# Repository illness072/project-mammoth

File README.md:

# Project 🦣

This keyboard was developed as a successor to the elephant42 and was originally planned to be released as mammoth42. However, during the development process, custom keyboards by other authors, Mammoth75 and Mammoth20, were released, and it seemed somewhat awkward to re-release the keyboard under the same name.
However, we could not give up our desire to use 🦣 as a companion to 🐘, so we decided to give it this name, taking care not to infringe on their names as much as possible.

# Still WIP, or Forever WIP?

This project is still in its infancy and is only about 20% of the way to the final product I have in mind. There are still a lot of unresolved bugs and issues, but even at this point, I think the keyboard is fun enough to use. Let's enjoy "being unfinished" together.

## Rough Milestones

1. [x] Works as USB HID with Pro Micro or as BLE HID with ISP1807micro and CR2032 battery.
1. [x] Operation as a left and right independent BLE device. The board might be modified to use Seeed XIAO BLE and the batteries might be modified to use NiMH rechargeable batteries.
1. [ ] Support for 34mm trackball.
1. (Still a secret.)

    :

## To be confirmed before manufacturing

The design currently uses two MCP23017-E/SS. These I/O expanders have long since been depleted from the market due to the recent semiconductor shortage and are currently priced at two to three times the normal price. To protect your wallet, it would be wise to wait for the stock to come back.

# BOM

## Main Boards

|Ref|Qty|Value or Part|Description|
|--|--|--|--|
||42|1N4148W|Fast Switching Diode|
||42|CPG151101S11-16|Kailh Switch Socket|
|U1,U2|2|MCP23017-E/SS|16-Bit I/O Expander|
||2|BM05B-ACHSS-A-GAN-ETF(LF)(SN)|JST ACH Connector 5P|

## Palm-rest Boards

|Ref|Qty|Value or Part|Description|
|--|--|--|--|
||2|BH-411-4P24|AAA Battery Holder|
||2|BM05B-ACHSS-A-GAN-ETF(LF)(SN)|JST ACH Connector 5P|
||2|SS-12D00G3|Slide Switch|
||2|Seeed Studio XIAO nRF52840||
|L1|2|100μH|Inductor|
|R1,R2|4|4.6kΩ|Resistor|
|C1|2|47μF|Capacitor|
|C2|2|22μF|Capacitor|
|D1|2|1S4|Schotky barrier diode|
|HT7733A|2|HT7733A|PFM Step-up DC/DC Converter|
|TRRS|0|MJ-4PP-9|TRRS Jack (Optional:2)|

## Cables

|Qty|Value or Part|Description|
|--|--|--|
|4|ACHR-05V-A-S|JST ACH Connector Housing 5P|
|10|01SACHSACH-30L-150|JST ACH Connector Contact(SACH-003G-P0.2) Cable|

# Where's the firmware?

Not yet.

# License?

Beerware!!

Come drink beer in Tokyo with me!! 🍺🍺🍺

# Poor English?

Sorry, it's DeepL Translate.

# [PR] Sponsored by PCBWay

Project 🦣 is currently prototyping with support from PCBWay (https://www.pcbway.com/).
We found the silks to be more accurate and beautiful than those of various PCB makers in the same price range.

If you are in doubt about which PCB manufacturer to manufacture, PCBWay, with its experience in manufacturing 🦣, may be a good choice.

Thanks a lot PCBWay!

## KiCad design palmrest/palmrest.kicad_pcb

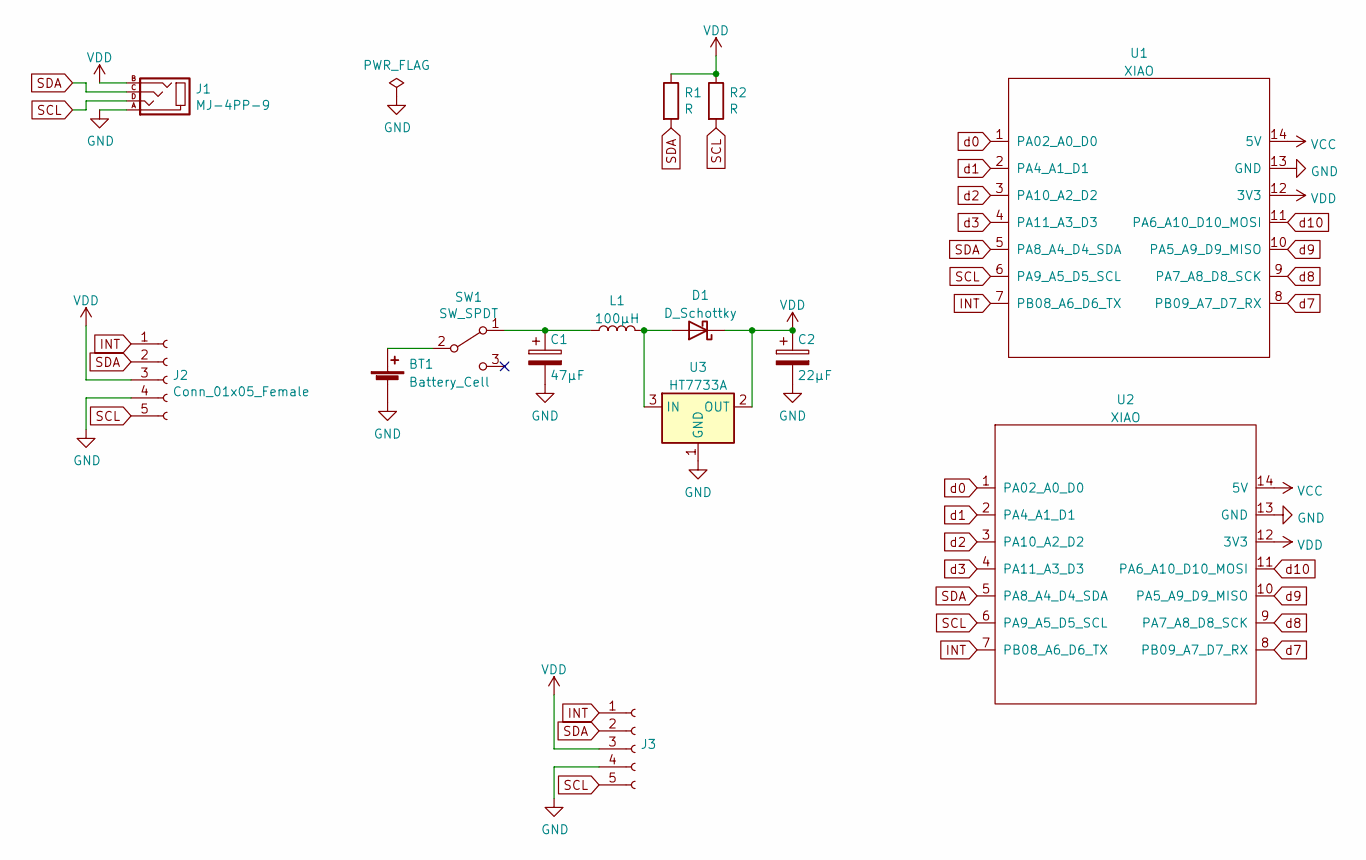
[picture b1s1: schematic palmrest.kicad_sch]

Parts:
BT1: Battery_Cell; bat_case_AAA
C1: 47μF; CP_Radial_D5.0mm_P2.00mm_P5.00mm_rev
C2: 22μF; CP_Radial_D5.0mm_P2.00mm_P5.00mm_rev
D1: D_Schottky; D_DO-34_SOD68_P7.62mm_Horizontal
J1: MJ-4PP-9
J2: Conn_01x05_Female; JST_ACH_BM05B-ACHSS-A-GAN-ETF_1x05-1MP_P1.20mm_Vertical_rev
J3: (no value)
L1: 100μH; L_Radial_D10.0mm_P5.00mm_Fastron_07M
R1, R2: R
SW1: SW_SPDT; SS-12D00G3
U1, U2: XIAO; Seeeduino XIAO-MOUDLE14P-2.54-21X17.8MM
U3: HT7733A

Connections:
GND: BT1.2 (-), C1.2, C2.2, J1.A, J2.4, J3.4, U1.13 (GND), U2.13 (GND), U3.1 (GND)
INT: J2.1, J3.1, U1.7 (PB08_A6_D6_TX), U2.7 (PB08_A6_D6_TX)
unnamed: BT1.1 (+), SW1.2 (B)
unnamed: C1.1, L1.1, SW1.1 (A)
unnamed: D1.2 (A), L1.2, U3.3 (IN)
SCL: J1.D, J2.5, J3.5, R2.2, U1.6 (PA9_A5_D5_SCL), U2.6 (PA9_A5_D5_SCL)
SDA: J1.C, J2.2, J3.2, R1.2, U1.5 (PA8_A4_D4_SDA), U2.5 (PA8_A4_D4_SDA)
VCC: U1.14 (5V), U2.14 (5V)
VDD: C2.1, D1.1 (K), J1.B, J2.3, J3.3, R1.1, R2.1, U1.12 (3V3), U2.12 (3V3), U3.2 (OUT)
d0: U1.1 (PA02_A0_D0), U2.1 (PA02_A0_D0)
d1: U1.2 (PA4_A1_D1), U2.2 (PA4_A1_D1)
d2: U1.3 (PA10_A2_D2), U2.3 (PA10_A2_D2)
d3: U1.4 (PA11_A3_D3), U2.4 (PA11_A3_D3)
d7: U1.8 (PB09_A7_D7_RX), U2.8 (PB09_A7_D7_RX)
d8: U1.9 (PA7_A8_D8_SCK), U2.9 (PA7_A8_D8_SCK)
d9: U1.10 (PA5_A9_D9_MISO), U2.10 (PA5_A9_D9_MISO)
d10: U1.11 (PA6_A10_D10_MOSI), U2.11 (PA6_A10_D10_MOSI)

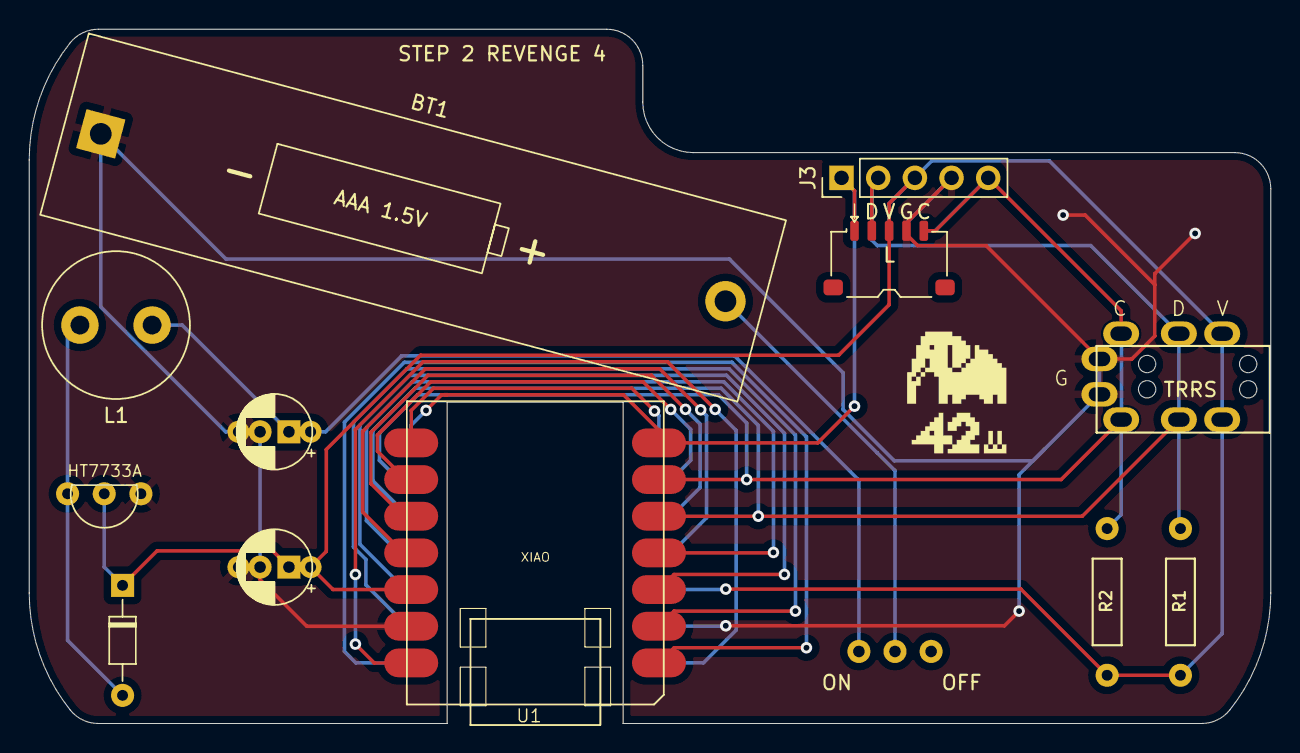
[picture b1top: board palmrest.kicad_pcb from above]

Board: 2 copper layers, 86.0 x 48.1 mm, 14 parts (1 on the bottom side), 17 nets.

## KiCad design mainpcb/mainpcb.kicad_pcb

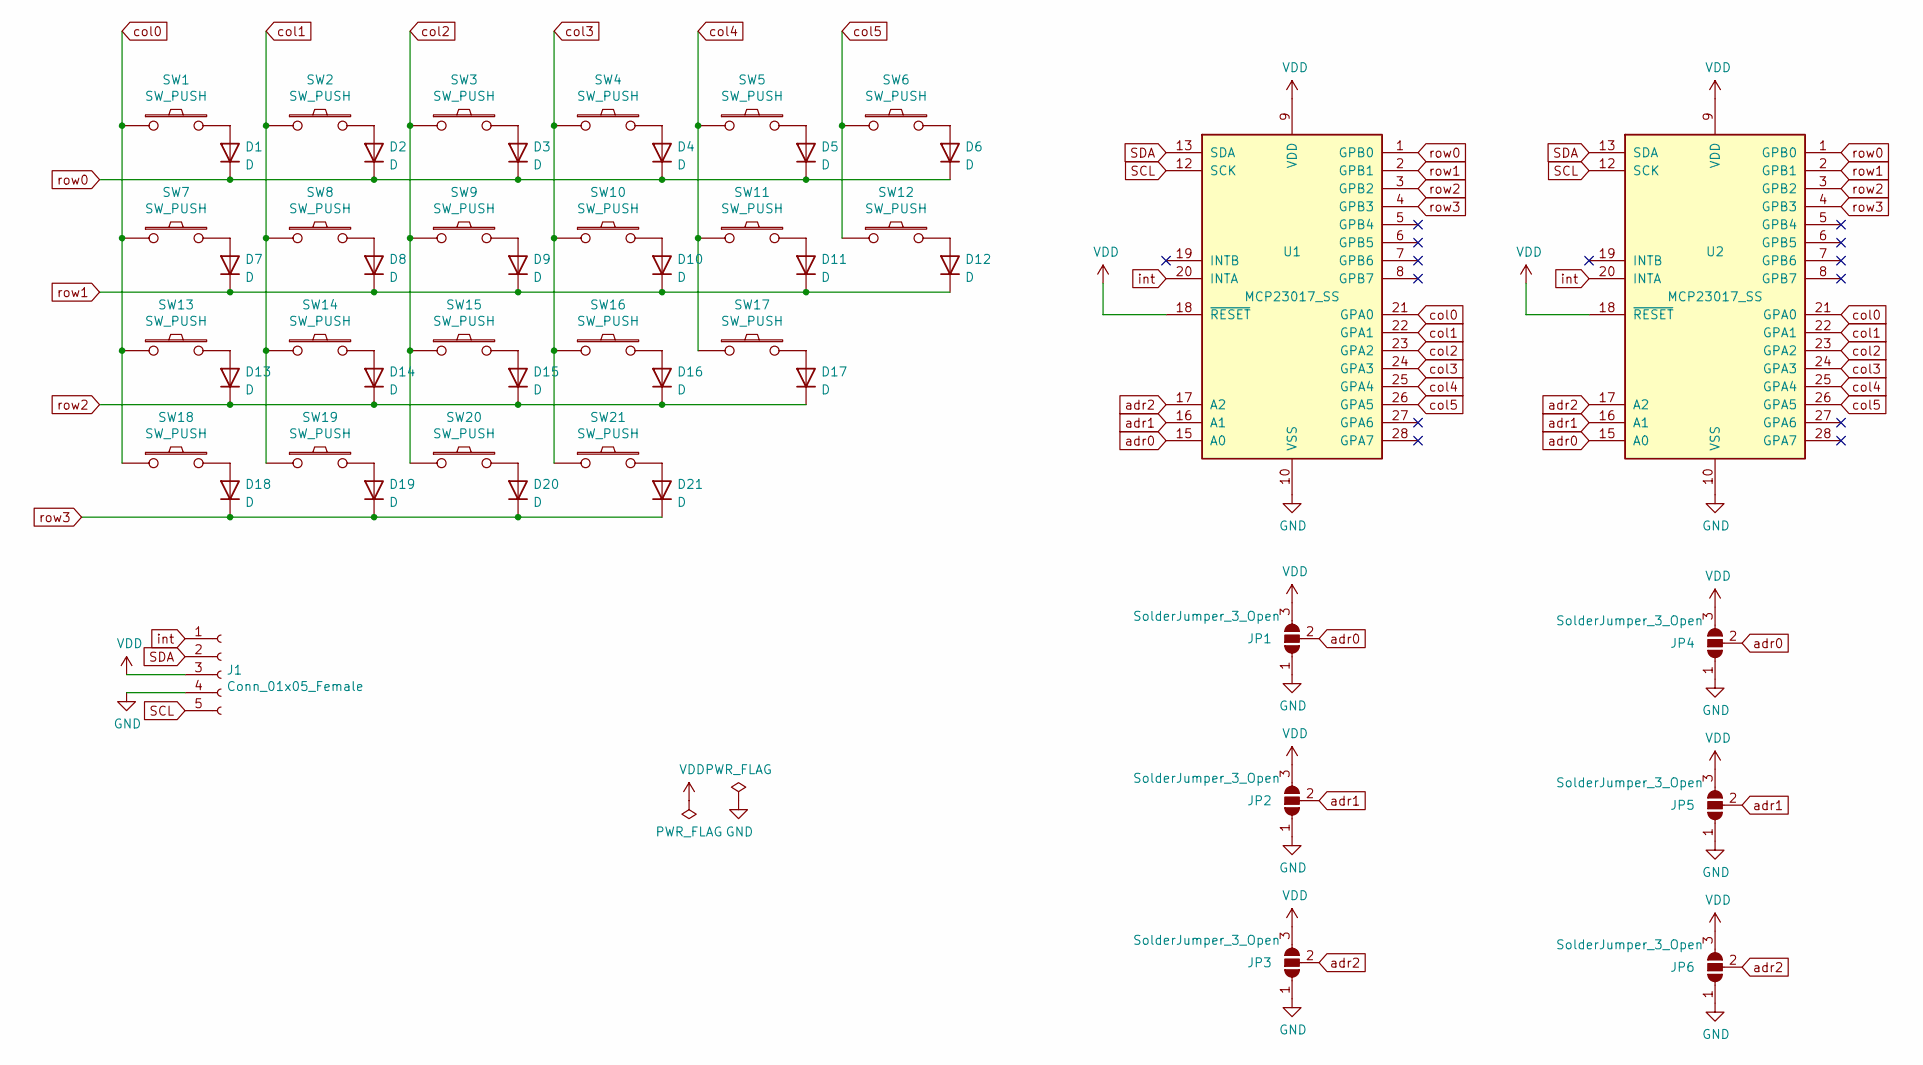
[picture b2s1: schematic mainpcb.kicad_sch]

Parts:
D1, D2, D3, D4, D5, D6, D7, D8, D9, D10, D11, D12, D13, D14, D15, D16, D17, D18, D19, D20, D21: D
J1: Conn_01x05_Female; JST_ACH_BM05B-ACHSS-A-GAN-ETF_1x05-1MP_P1.20mm_Vertical_rev
JP1, JP2, JP3, JP4, JP5, JP6: SolderJumper_3_Open; SolderJumper-3_P1.3mm_Open_Pad1.0x1.5mm
SW1, SW2, SW3, SW4, SW5, SW6, SW7, SW8, SW9, SW10, SW11, SW12, SW13, SW14, SW15, SW16, SW17, SW18, SW19, SW20, SW21: SW_PUSH; MX_Hotswap_R_1u
U1, U2: MCP23017_SS; SSOP-28_5.3x10.2mm_P0.65mm

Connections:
GND: J1.4, JP1.1 (A), JP2.1 (A), JP3.1 (A), JP4.1 (A), JP5.1 (A), JP6.1 (A), U1.10 (VSS), U2.10 (VSS)
unnamed: D1.2 (A), SW1.2
unnamed: D2.2 (A), SW2.2
unnamed: D3.2 (A), SW3.2
unnamed: D4.2 (A), SW4.2
unnamed: D5.2 (A), SW5.2
unnamed: D6.2 (A), SW6.2
unnamed: D7.2 (A), SW7.2
unnamed: D8.2 (A), SW8.2
unnamed: D9.2 (A), SW9.2
unnamed: D10.2 (A), SW10.2
unnamed: D11.2 (A), SW11.2
unnamed: D12.2 (A), SW12.2
unnamed: D13.2 (A), SW13.2
unnamed: D14.2 (A), SW14.2
unnamed: D15.2 (A), SW15.2
unnamed: D16.2 (A), SW16.2
unnamed: D17.2 (A), SW17.2
unnamed: D18.2 (A), SW18.2
unnamed: D19.2 (A), SW19.2
unnamed: D20.2 (A), SW20.2
unnamed: D21.2 (A), SW21.2
SCL: J1.5, U1.12 (SCK), U2.12 (SCK)
SDA: J1.2, U1.13 (SDA), U2.13 (SDA)
VDD: J1.3, JP1.3 (B), JP2.3 (B), JP3.3 (B), JP4.3 (B), JP5.3 (B), JP6.3 (B), U1.9 (VDD), U1.18 (~RESET), U2.9 (VDD), U2.18 (~RESET)
adr0: JP1.2 (C), JP4.2 (C), U1.15 (A0), U2.15 (A0)
adr1: JP2.2 (C), JP5.2 (C), U1.16 (A1), U2.16 (A1)
adr2: JP3.2 (C), JP6.2 (C), U1.17 (A2), U2.17 (A2)
col0: SW1.1, SW7.1, SW13.1, SW18.1, U1.21 (GPA0), U2.21 (GPA0)
col1: SW2.1, SW8.1, SW14.1, SW19.1, U1.22 (GPA1), U2.22 (GPA1)
col2: SW3.1, SW9.1, SW15.1, SW20.1, U1.23 (GPA2), U2.23 (GPA2)
col3: SW4.1, SW10.1, SW16.1, SW21.1, U1.24 (GPA3), U2.24 (GPA3)
col4: SW5.1, SW11.1, SW17.1, U1.25 (GPA4), U2.25 (GPA4)
col5: SW6.1, SW12.1, U1.26 (GPA5), U2.26 (GPA5)
int: J1.1, U1.20 (INTA), U2.20 (INTA)
row0: D1.1 (K), D2.1 (K), D3.1 (K), D4.1 (K), D5.1 (K), D6.1 (K), U1.1 (GPB0), U2.1 (GPB0)
row1: D7.1 (K), D8.1 (K), D9.1 (K), D10.1 (K), D11.1 (K), D12.1 (K), U1.2 (GPB1), U2.2 (GPB1)
row2: D13.1 (K), D14.1 (K), D15.1 (K), D16.1 (K), D17.1 (K), U1.3 (GPB2), U2.3 (GPB2)
row3: D18.1 (K), D19.1 (K), D20.1 (K), D21.1 (K), U1.4 (GPB3), U2.4 (GPB3)

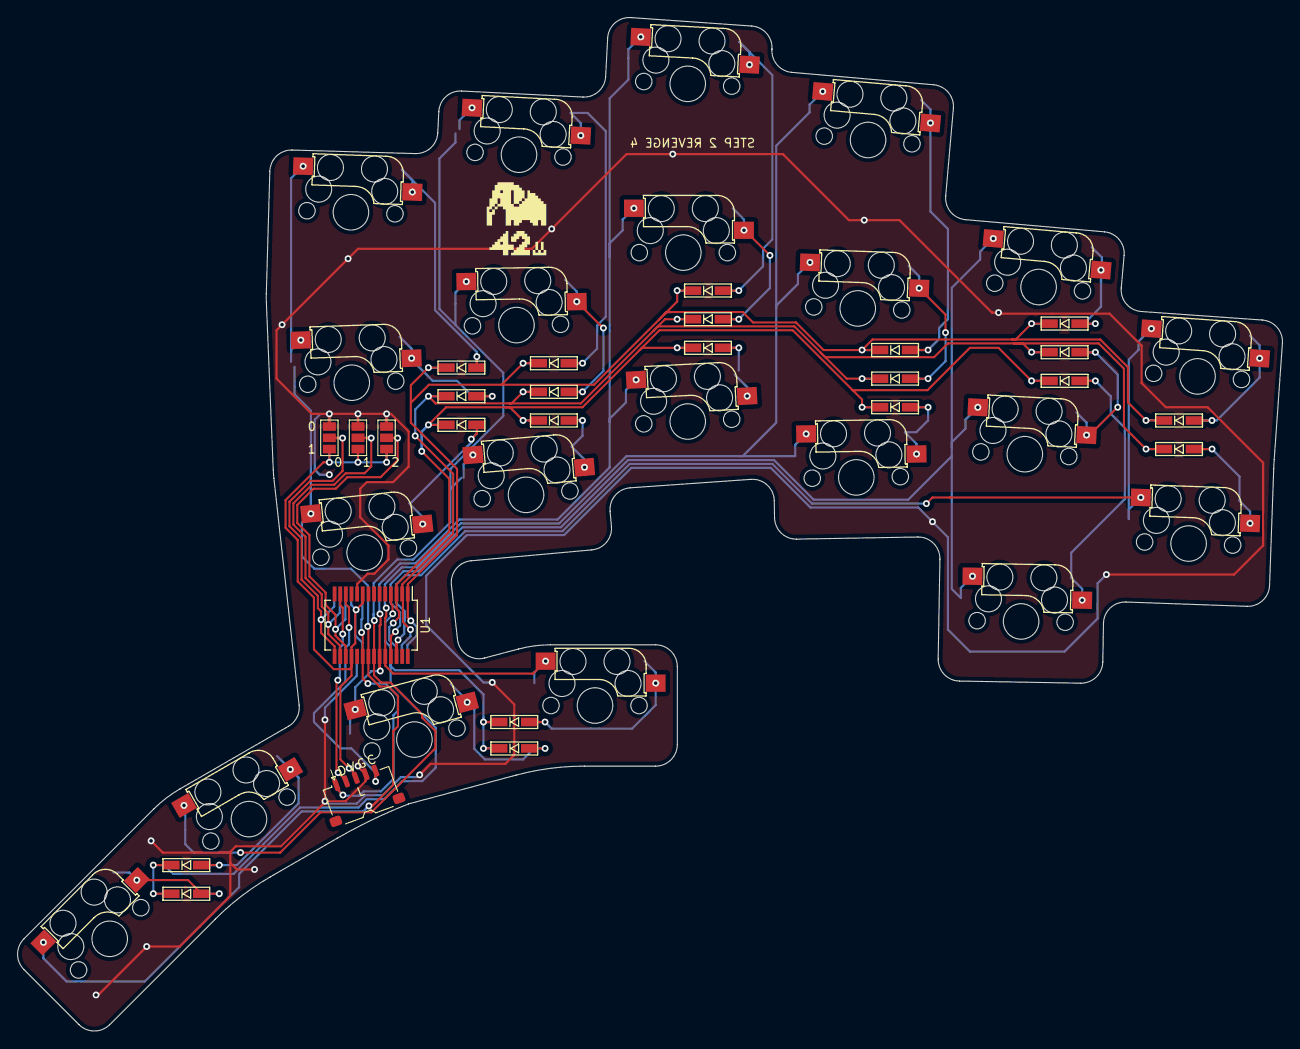
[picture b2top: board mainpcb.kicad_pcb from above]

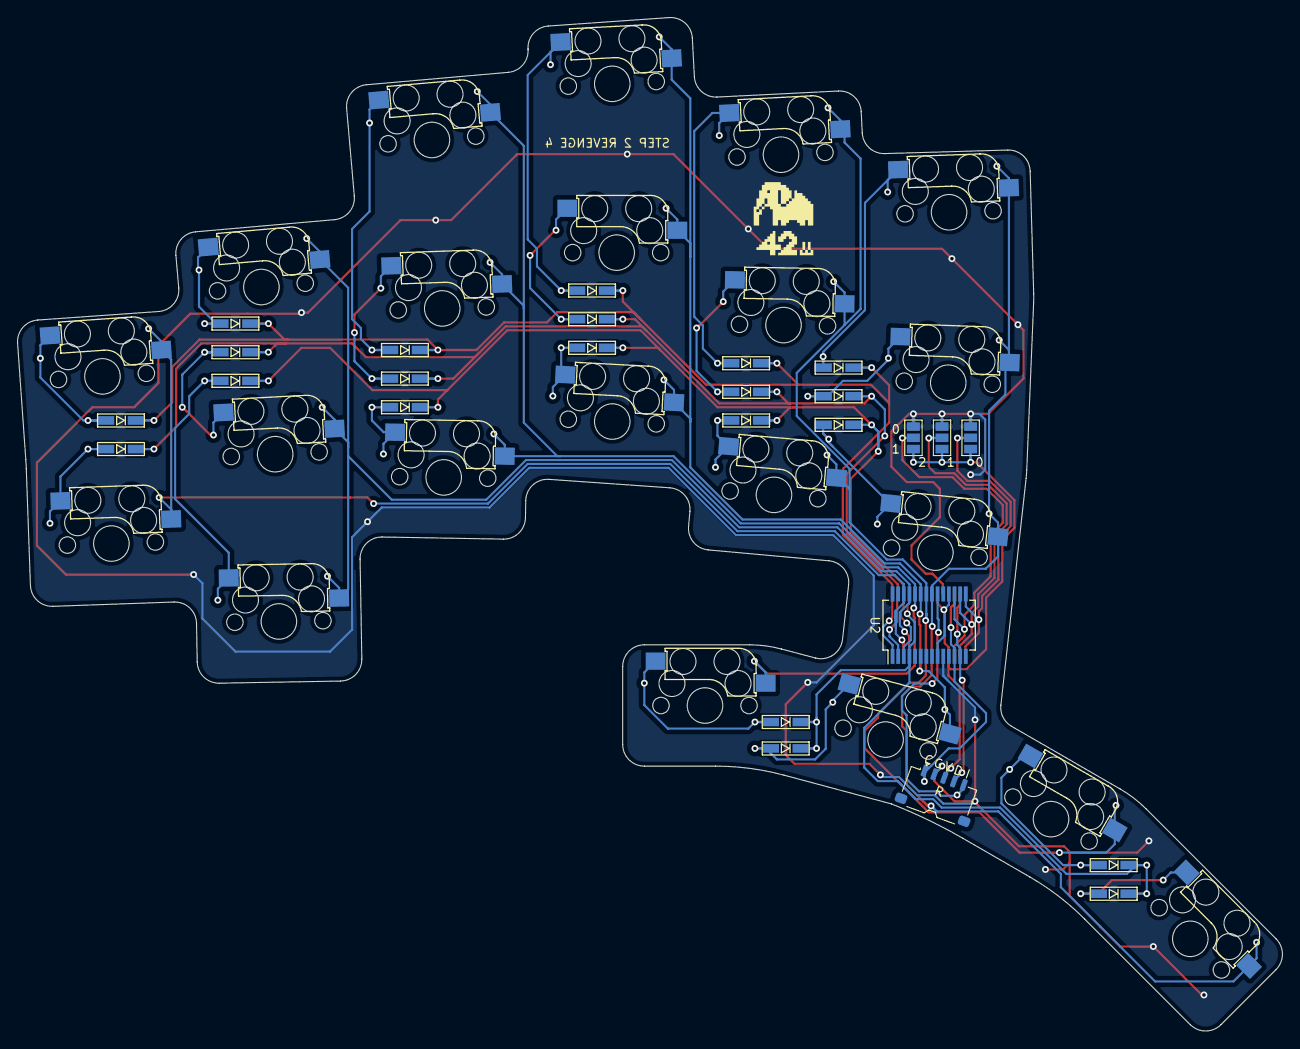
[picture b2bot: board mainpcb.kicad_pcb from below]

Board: 2 copper layers, 146.0 x 116.9 mm, 51 parts (4 on the bottom side), 39 nets.

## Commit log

2022-05-05 Update README.md
    s/seeduino/seeed/
2022-06-21 key-matrix using single mcp23017
2022-06-21 revenge3
2022-06-21 fix footprint
2022-06-21 The results of Revenge 3 were recorded in README.
2022-06-21 remove private path
2022-07-19 revenge 4
2022-08-04 add gerber dir to gitignore
2022-08-04 update models
2022-09-19 add BOM
